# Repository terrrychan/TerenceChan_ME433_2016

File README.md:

Terence Chan
March 31st, 2016
Mechatronics Git Account

New added line

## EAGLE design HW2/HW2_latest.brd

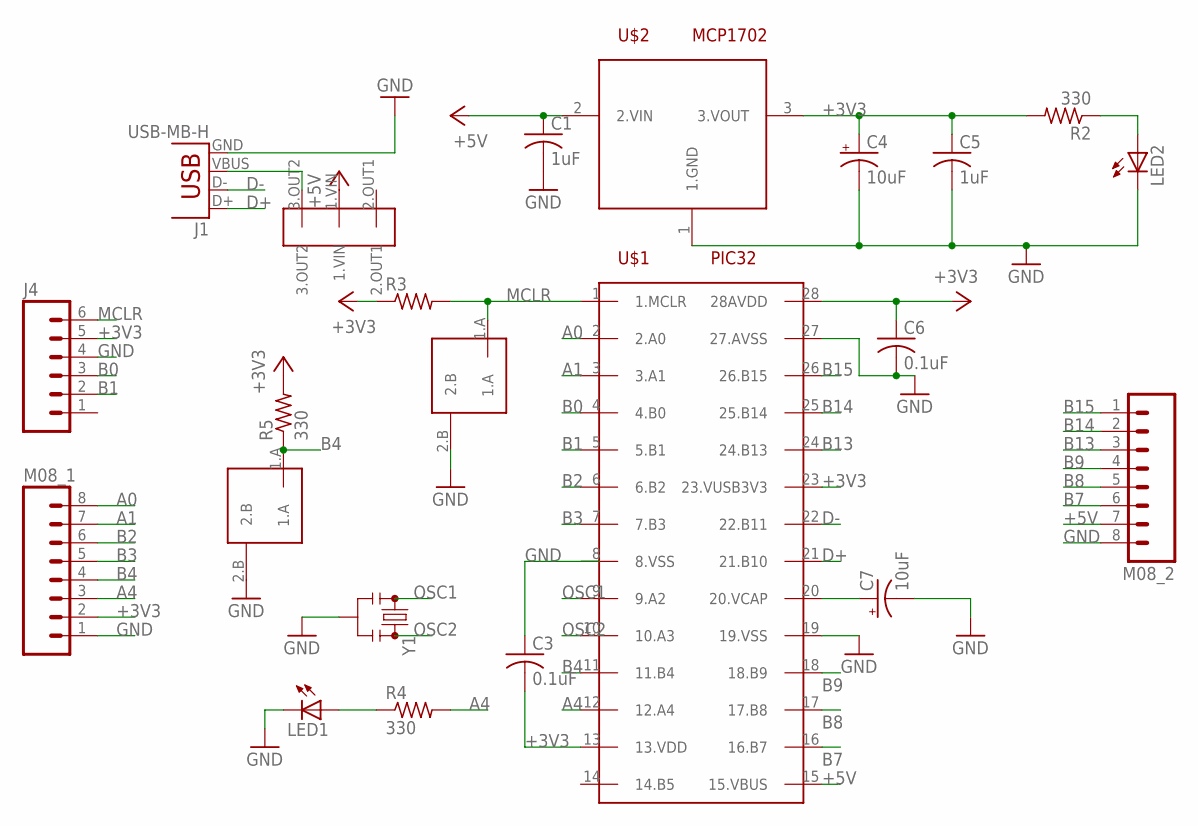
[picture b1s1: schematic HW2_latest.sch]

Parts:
C1, C5: 1uF; C025-024X044
C3, C6: 0.1uF; C025-024X044
C4, C7: 10uF; TT2D4
J1: USB-MB-H
J4: M06SILK_FEMALE_PTH; 1X06
LED1, LED2: LED3MM
M08_1, M08_2: M08; 1X08_ROUND
R2, R4, R5: 330; 0207/10
R3: R-US_0207/10; 0207/10
U$1: PIC32; DIL28-3
U$2: MCP1702; TO92
U$3: SLIDE_SWITCH
U$4, U$5: PUSH_BUTTON
Y1: RESONATORPTH; RESONATOR-PTH

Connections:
+3V3: C3.2, C4.+, C5.1, C6.1, J4.5, M08_1.2, R2.2, R3.1, R5.2, U$1.13 (13.VDD), U$1.23 (23.VUSB3V3), U$1.28 (28AVDD), U$2.3 (3.VOUT)
+5V: C1.1, M08_2.7, U$1.15 (15.VBUS), U$2.2 (2.VIN), U$3.1.VIN
A0: M08_1.8, U$1.2 (2.A0)
A1: M08_1.7, U$1.3 (3.A1)
A4: M08_1.3, R4.2, U$1.12 (12.A4)
B0: J4.3, U$1.4 (4.B0)
B1: J4.2, U$1.5 (5.B1)
B2: M08_1.6, U$1.6 (6.B2)
B3: M08_1.5, U$1.7 (7.B3)
B4: M08_1.4, R5.1, U$1.11 (11.B4), U$5.1.A
B7: M08_2.6, U$1.16 (16.B7)
B8: M08_2.5, U$1.17 (17.B8)
B9: M08_2.4, U$1.18 (18.B9)
B13: M08_2.3, U$1.24 (24.B13)
B14: M08_2.2, U$1.25 (25.B14)
B15: M08_2.1, U$1.26 (26.B15)
D+: J1.D+, U$1.21 (21.B10)
D-: J1.D-, U$1.22 (22.B11)
GND: C1.2, C3.1, C4.-, C5.2, C6.2, C7.-, J1.GND, J4.4, LED1.K (C), LED2.K (C), M08_1.1, M08_2.8, U$1.19 (19.VSS), U$1.27 (27.AVSS), U$2.1 (1.GND), U$4.2.B, U$5.2.B, Y1.2
MCLR: J4.6, R3.2, U$1.1 (1.MCLR), U$4.1.A
unnamed: LED1.A, R4.1
unnamed: LED2.A, R2.1
unnamed: J1.VBUS, U$3.3.OUT2
unnamed: C7.+, U$1.20 (20.VCAP)
OSC1: U$1.9 (9.A2), Y1.1
OSC2: U$1.10 (10.A3), Y1.3

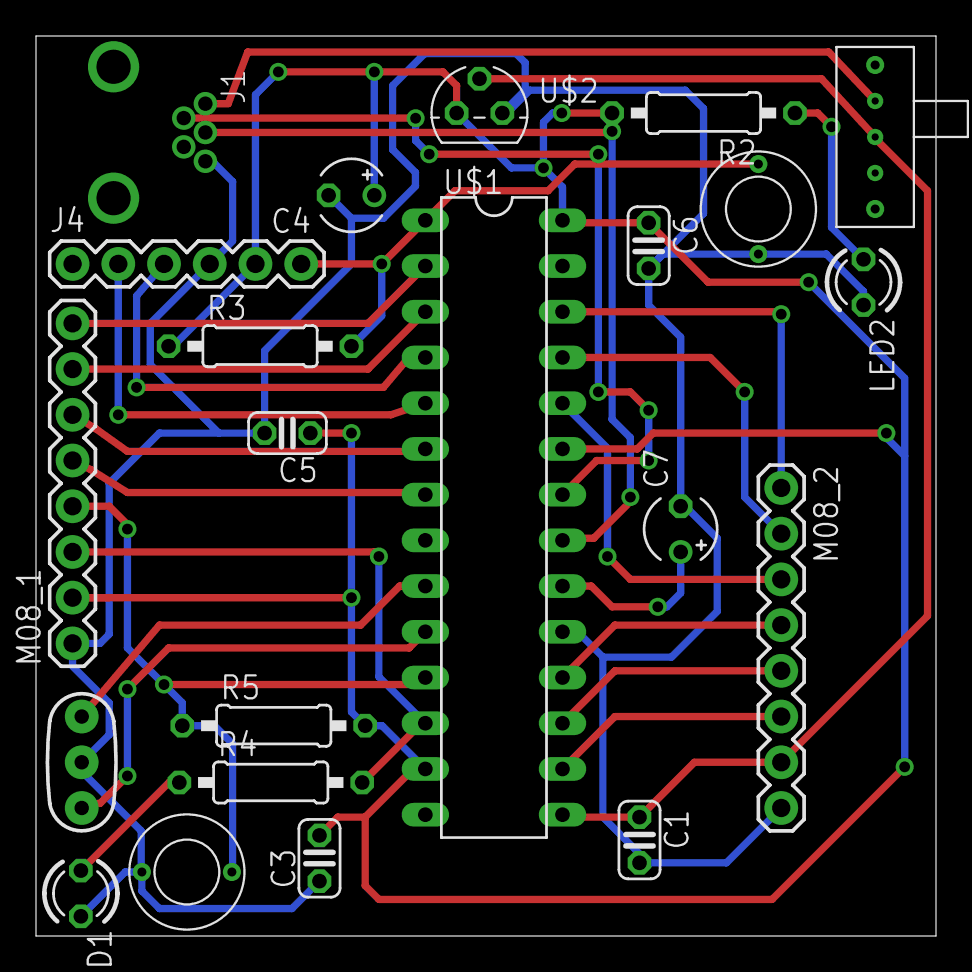
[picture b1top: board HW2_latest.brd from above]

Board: 2 copper layers, 50.0 x 50.0 mm, 22 parts (0 on the bottom side), 26 nets.

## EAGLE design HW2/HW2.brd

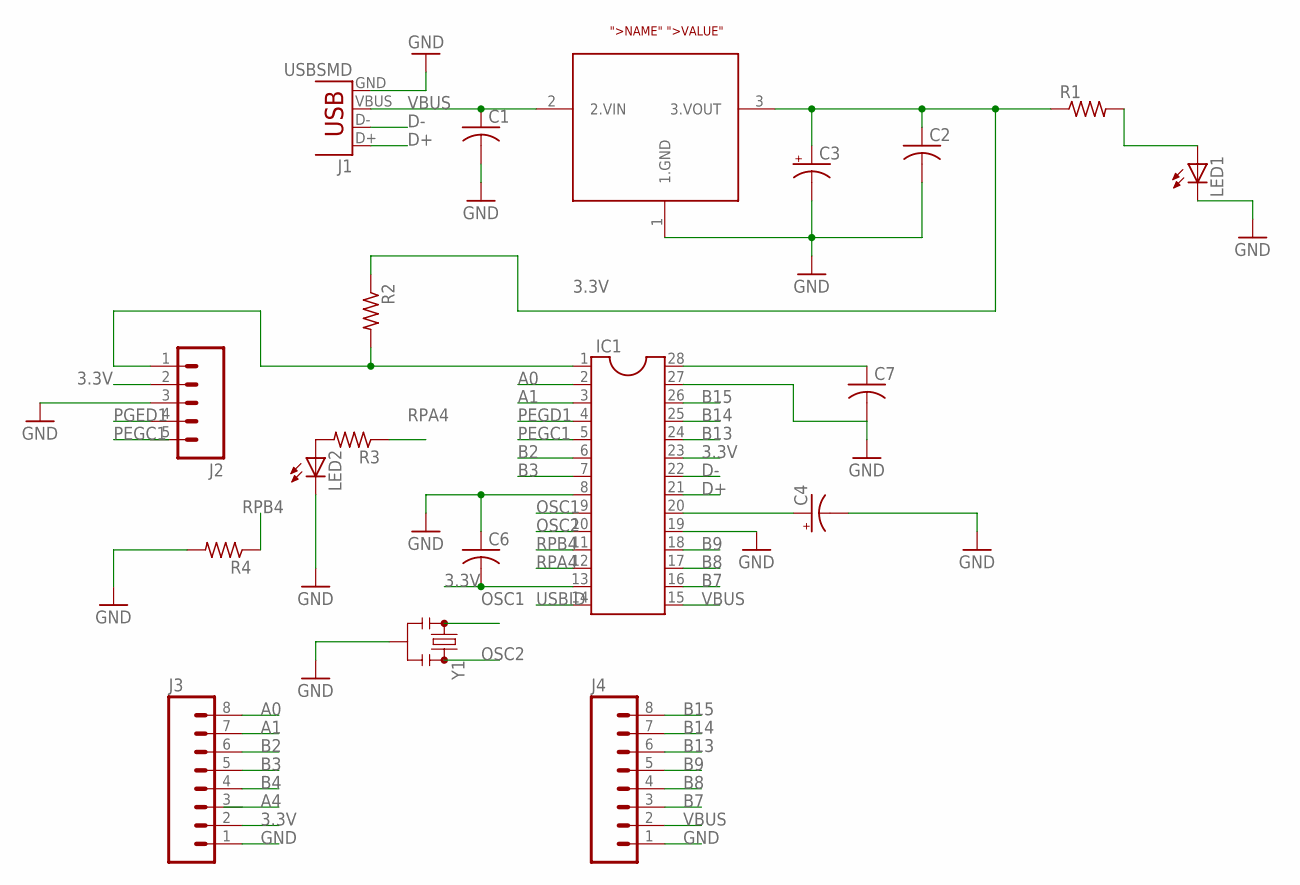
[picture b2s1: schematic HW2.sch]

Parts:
C1, C2, C6, C7: C-US050-024X044; C050-024X044
C3, C4: CPOL-USE2-5; E2-5
IC1: DIL28-4
J1: USBSMD; USB-MINIB
J2: M05JST; JST-5-PTH
J3, J4: M08NO_SILK_FEMALE_PTH; 1X08_NO_SILK
LED1, LED2: LED3MM
R1, R2, R3, R4: R-US_0207/10; 0207/10
U$1: MCP1702; TO92
Y1: RESONATORPTH; RESONATOR-PTH

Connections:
3.3V: C2.1, C3.+, C6.2, C7.1, IC1.13, IC1.23, IC1.28, J2.2, J3.2, R1.1, R2.1, U$1.3 (3.VOUT)
A0: IC1.2, J3.8
A1: IC1.3, J3.7
B2: IC1.6, J3.6
B3: IC1.7, J3.5
B4: J3.4
B7: IC1.16, J4.3
B8: IC1.17, J4.4
B9: IC1.18, J4.5
B13: IC1.24, J4.6
B14: IC1.25, J4.7
B15: IC1.26, J4.8
D+: IC1.21, J1.D+
D-: IC1.22, J1.D-
GND: C1.2, C2.2, C3.-, C4.-, C6.1, IC1.8, IC1.19, J1.GND, J2.3, J3.1, J4.1, LED1.K (C), LED2.K (C), R4.2, U$1.1 (1.GND), Y1.2
unnamed: C7.2, IC1.27
unnamed: LED2.A, R3.2
unnamed: LED1.A, R1.2
unnamed: IC1.1, J2.1, R2.2
unnamed: C4.+, IC1.20
OSC1: IC1.9, Y1.1
OSC2: IC1.10, Y1.3
PEGC1: IC1.5
PEGD1: IC1.4
PGED1: J2.4
RPA4: IC1.12, R3.1
RPB4: IC1.11, R4.1
USBID: IC1.14
VBUS: C1.1, IC1.15, J1.VBUS, J4.2, U$1.2 (2.VIN)

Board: 2 copper layers, 19 parts (0 on the bottom side), 24 nets, no tracks yet.

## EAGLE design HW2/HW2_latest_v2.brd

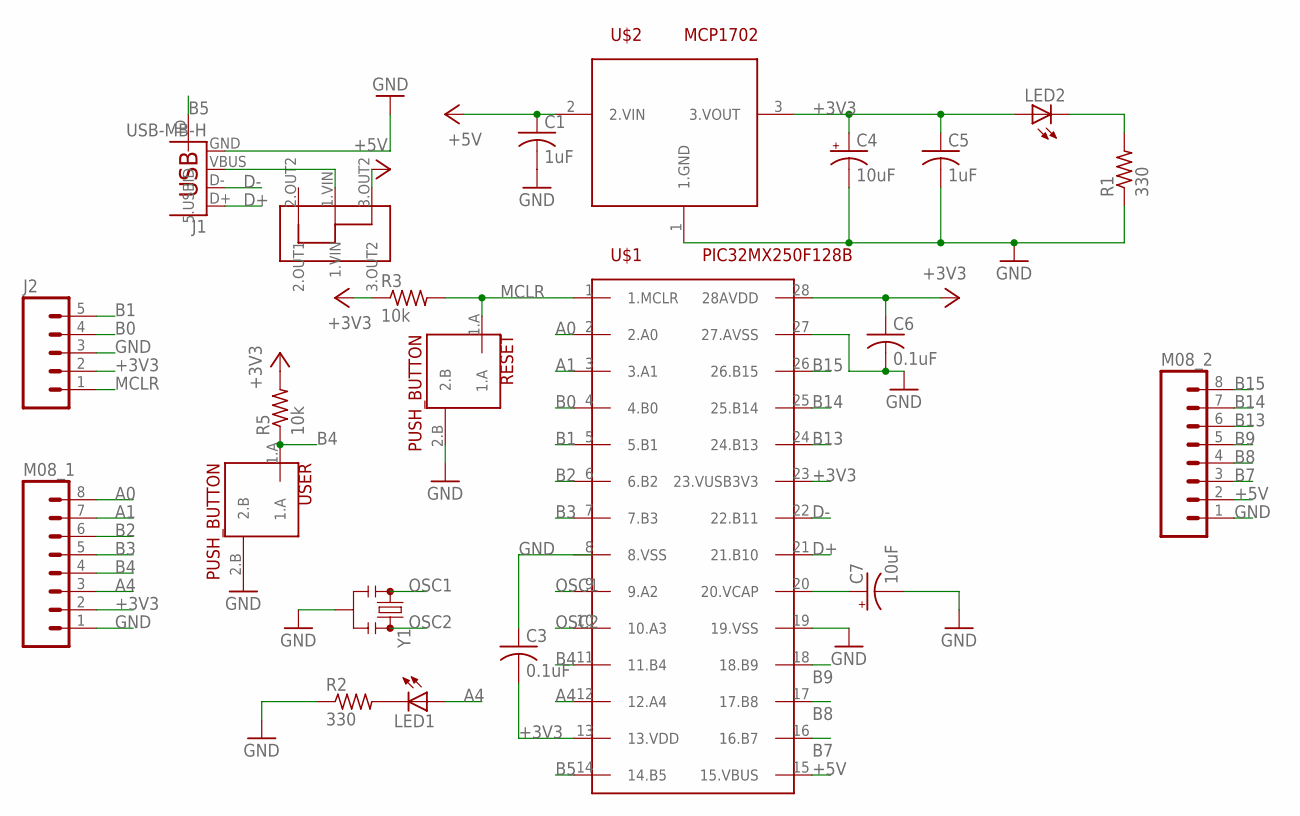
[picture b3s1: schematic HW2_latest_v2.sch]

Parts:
C1, C5: 1uF; C025-024X044
C3, C6: 0.1uF; C025-024X044
C4, C7: 10uF; TT2D4
J1: USB-MB-H
J2: M05PTH; 1X05
LED1, LED2: LED3MM
M08_1, M08_2: M08; 1X08_ROUND
R1, R2: 330; 0207/10
R3, R5: 10k; 0207/10
RESET: PUSH_BUTTON
U$1: PIC32MX250F128B; DIL28-3
U$2: MCP1702; TO92
U$3: SLIDE_SWITCH
USER: PUSH_BUTTON
Y1: RESONATORPTH; RESONATOR-PTH

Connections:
+3V3: C3.2, C4.+, C5.1, C6.1, J2.2, LED2.A, M08_1.2, R3.1, R5.2, U$1.13 (13.VDD), U$1.23 (23.VUSB3V3), U$1.28 (28AVDD), U$2.3 (3.VOUT)
+5V: C1.1, M08_2.2, U$1.15 (15.VBUS), U$2.2 (2.VIN), U$3.3.OUT2
A0: M08_1.8, U$1.2 (2.A0)
A1: M08_1.7, U$1.3 (3.A1)
A4: LED1.A, M08_1.3, U$1.12 (12.A4)
B0: J2.4, U$1.4 (4.B0)
B1: J2.5, U$1.5 (5.B1)
B2: M08_1.6, U$1.6 (6.B2)
B3: M08_1.5, U$1.7 (7.B3)
B4: M08_1.4, R5.1, U$1.11 (11.B4), USER.1.A
B5: J1.ID (5.USBID), U$1.14 (14.B5)
B7: M08_2.3, U$1.16 (16.B7)
B8: M08_2.4, U$1.17 (17.B8)
B9: M08_2.5, U$1.18 (18.B9)
B13: M08_2.6, U$1.24 (24.B13)
B14: M08_2.7, U$1.25 (25.B14)
B15: M08_2.8, U$1.26 (26.B15)
D+: J1.D+, U$1.21 (21.B10)
D-: J1.D-, U$1.22 (22.B11)
GND: C1.2, C3.1, C4.-, C5.2, C6.2, C7.-, J1.GND, J2.3, M08_1.1, M08_2.1, R1.1, R2.1, RESET.2.B, U$1.19 (19.VSS), U$1.27 (27.AVSS), U$2.1 (1.GND), USER.2.B, Y1.2
MCLR: J2.1, R3.2, RESET.1.A, U$1.1 (1.MCLR)
unnamed: LED1.K (C), R2.2
unnamed: LED2.K (C), R1.2
unnamed: J1.VBUS, U$3.1.VIN
unnamed: C7.+, U$1.20 (20.VCAP)
OSC1: U$1.9 (9.A2), Y1.1
OSC2: U$1.10 (10.A3), Y1.3

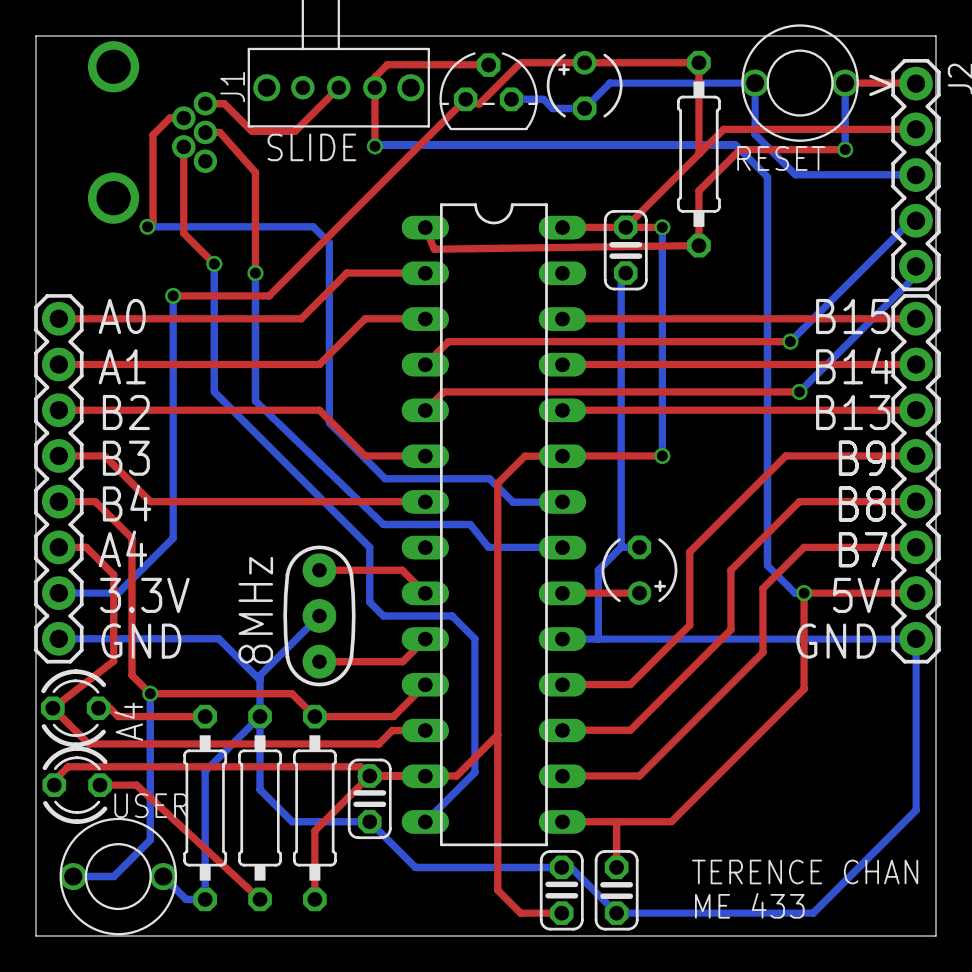
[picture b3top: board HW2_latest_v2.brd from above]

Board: 2 copper layers, 50.0 x 50.0 mm, 22 parts (0 on the bottom side), 27 nets.

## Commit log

2016-03-31 :boom::camel: Added .gitattributes
2016-03-31 My first commit!
2016-03-31 Added a new line
2016-04-01 DEVCFG0
2016-04-01 DEVCFG1
2016-04-01 DEVCFG2
2016-04-01 DEVCFG3
2016-04-03 Initialized pushbutton and LED
2016-04-04 LED 1kHz + Pushbutton
2016-04-04 Picture of breadboard
2016-04-04 Picture of Voltage Regulator Oscillations
2016-04-07 Board - still needs to be modified so wires aren't crossing
2016-04-07 Pushbutton/Slide/DIP need to be added, # of PINs double checked
2016-04-07 Figure out device/package
2016-04-12 Final Board, all connections made - needs error checking
2016-04-12 Final library for PIC32
2016-04-12 Final schematic for PIC32
2016-04-12 Extra files related to library/schematic/board
2016-04-14 Library updated to reflect final board/parts
2016-04-14 Final board for PIC32 - updated
2016-04-14 Ready to be checked before order
2016-04-14 Revert "Ready to be checked before order"
    This reverts commit afe56f701ebee319f2c8194212bc48b717578094.
2016-04-14 Extra Files created by Eagle when updating board/library/schematic
2016-04-14 Revert "Final board for PIC32 - updated"
    This reverts commit d253f6572f85d1bfdb04a65b19aa80cdc34b0d53.
2016-04-14 Revert "Final schematic for PIC32"
    This reverts commit ac4cd0e2b2bd768a499f1acb168f297e26ad0bf8.
2016-04-14 Ready to checked before order
2016-04-14 V2 is the latest one
2016-04-21 SPI working - 10 Hz Sine wave and 5 Hz Triangle Wave
2016-04-21 Cleaning up and adding comments to SPI code
2016-04-21 10 Hz Sine wave and 5 Hz Triangle Wave
2016-04-21 LED not powered, set- and getExpander a little buggy
2016-04-21 Picture of board - before working
2016-04-21 HW4 Done, SPI and I2C working
2016-04-21 Video of LED blinking according to push button
2016-04-21 MPLAB project files
2016-04-21 Repo renamed to HW4
2016-04-26 Minor edit - Changed line 124 -- Equivalent command to set pin low
2016-04-26 Gyro + Accel working!
2016-04-26 Displaying change in OC1 (pin B15) from X accel
2016-04-26 Final documented code w/ comments, everything working
2016-05-06 'Hello World 1337' working with LCD
2016-05-06 Hello World 1337 on LCD
2016-05-06 Updated to display IMU data on LCD
2016-05-10 Started Mouse Control
2016-05-10 Deleted unused function prototype
2016-05-11 IMU + PIC working as mouse
2016-05-12 Decreased delay and fixed orientation
2016-05-12 Starting CDC - PIC showing up as port COM3
2016-05-13 Updating Slider Bar App working!
2016-05-26 Basic CDC communication working -- printing on PuTTY screen
2016-05-30 Raw accelerometer values - x direction
2016-05-30 Camera app + slider bars
2016-05-31 COM visualization implemented -- need to fix CDC still
2016-05-31 Reorganized code + added COM2 text
2016-05-31 Starting CDC --- Errors debugged
2016-05-31 Two green thresholding sections working!
2016-06-07 Robot with android app and PIC program working! Everything uploaded
2016-06-07 Racer Code working! Text file describes how the motors are being controlled
2016-06-07 Android Tech Cup App working, photo of app layout included
    App contains two sets of 50 pixels searched to compute the average COM.
2016-06-07 Wheel designed and printed
2016-06-07 Hello World App working
2016-06-07 PIC USB CDC working -- printing raw XL values
2016-06-07 Mouse program working
    -- left tilt = to the left
    -- front tilt = going up
2016-06-09 IMU with duty cycle working
2016-06-09 LCD working
2016-06-09 DAC and I2C working
2016-06-09 Board and Libraries Uploaded
2016-06-09 Android Camera App camera
2016-06-09 First PIC Program working
2016-06-09 Files rearranged
2016-06-09 CDC app working - LED changing according to duty cycle from slider
2016-06-09 DXF Files + Screenshots uploaded
2016-06-09 APP_Tasks changed to void
2016-06-09 Added image to show mat is being tracked
2016-06-09 Added additional pictures of camera app
